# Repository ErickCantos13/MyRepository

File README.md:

# SensorEffector DMX Light Repository

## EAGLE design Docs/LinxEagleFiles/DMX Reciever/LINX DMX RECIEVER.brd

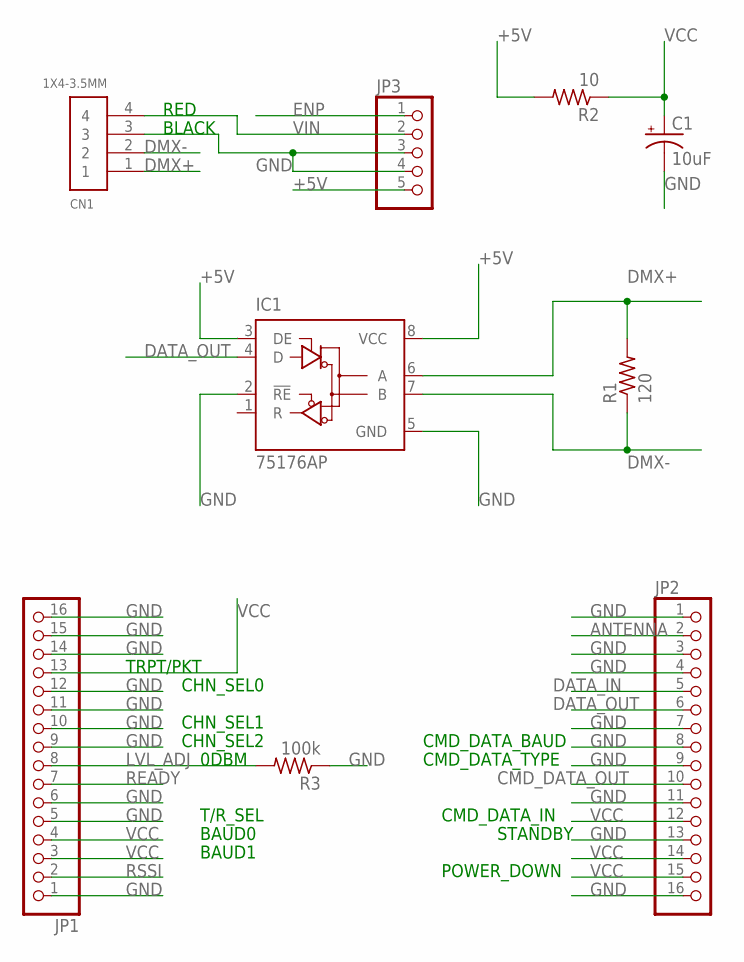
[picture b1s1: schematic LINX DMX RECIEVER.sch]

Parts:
C1: 10uF; B45181A
CN1: 1X4-3.5MM; 1X04-3.5MM
IC1: 75176AP; DIL08
JP1, JP2: PINHD-1X16; 1X16
JP3: PINHD-1X5/90; 1X05/90
R1: 120; 0414/15
R2: 10; 0414/15
R3: 100k; 0414/15

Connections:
+5V: IC1.3 (DE), IC1.8 (VCC), JP3.5, R2.2
ANTENNA: JP2.2
CMD_DATA_OUT: JP2.10
DATA_IN: JP2.5
DATA_OUT: IC1.4 (D), JP2.6
DMX+: CN1.1, IC1.6 (A), R1.2
DMX-: CN1.2, IC1.7 (B), R1.1
ENP: JP3.1
GND: C1.-, CN1.3, IC1.2 (!RE), IC1.5 (GND), JP1.1, JP1.5, JP1.6, JP1.9, JP1.10, JP1.11, JP1.12, JP1.14, JP1.15, JP1.16, JP2.1, JP2.3, JP2.4, JP2.7, JP2.8, JP2.9, JP2.11, JP2.13, JP2.16, JP3.3, JP3.4, R3.1
LVL_ADJ: JP1.8, R3.2
READY: JP1.7
RSSI: JP1.2
VCC: C1.+, JP1.3, JP1.4, JP1.13, JP2.12, JP2.14, JP2.15, R2.1
VIN: CN1.4, JP3.2

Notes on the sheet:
RED
BLACK
TRPT/PKT
CHN_SEL0
CHN_SEL1
CHN_SEL2
0DBM
T/R_SEL
BAUD0
BAUD1
STANDBY
POWER_DOWN
CMD_DATA_BAUD
CMD_DATA_TYPE
CMD_DATA_IN

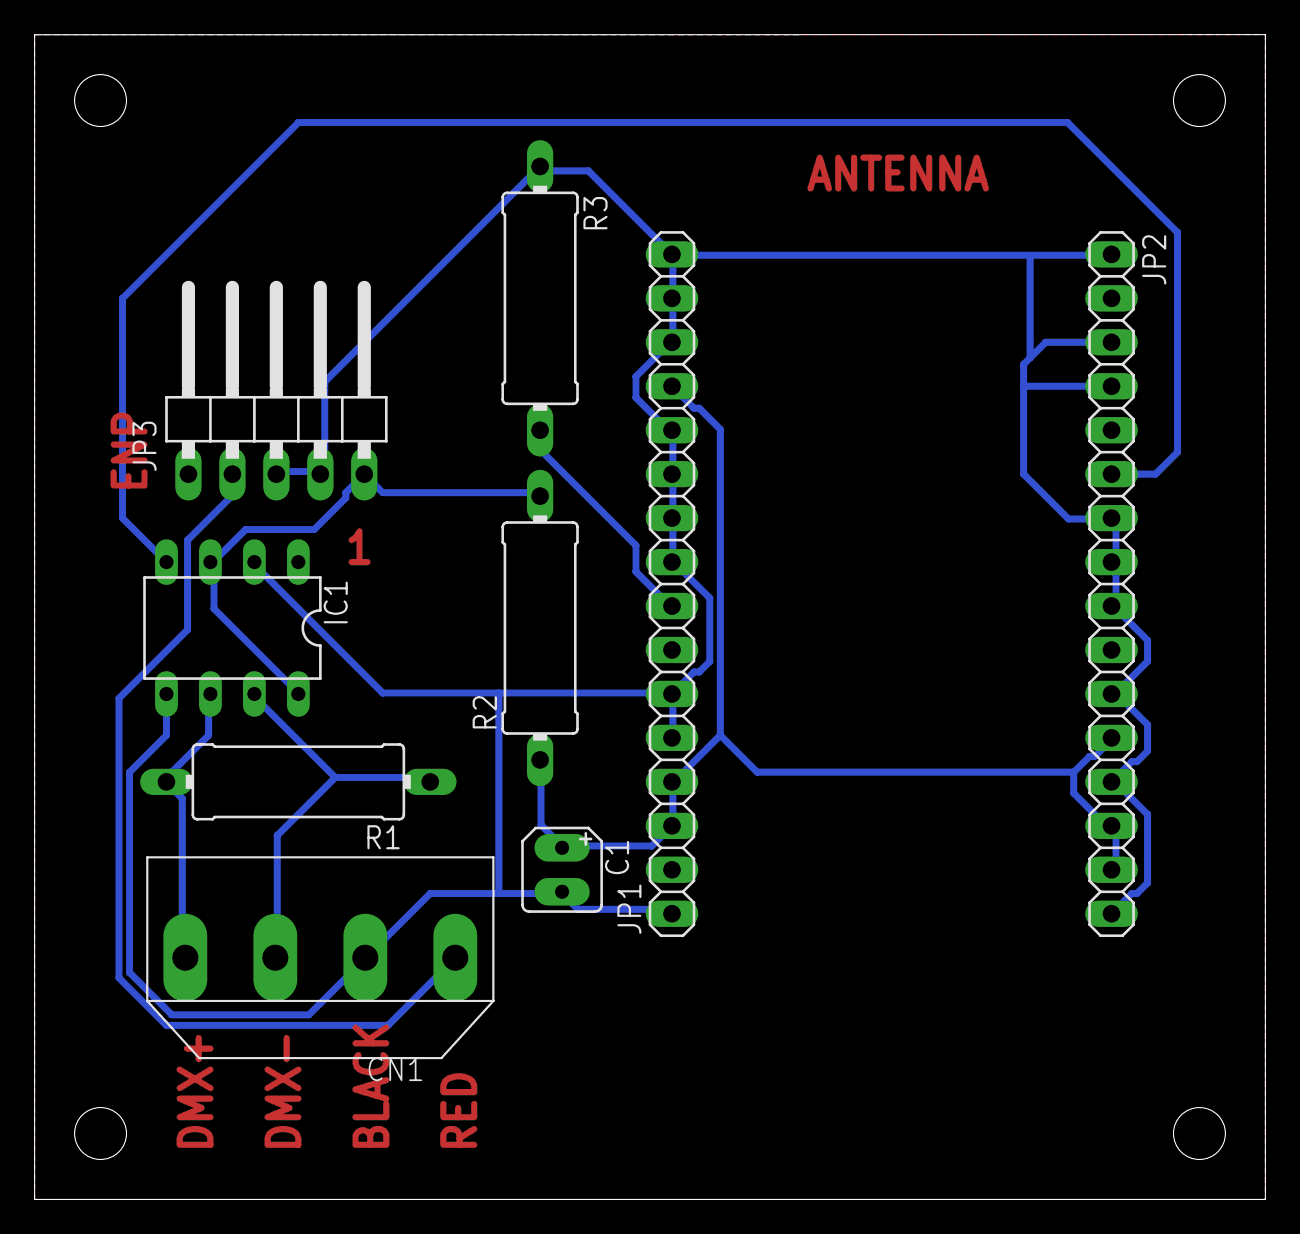
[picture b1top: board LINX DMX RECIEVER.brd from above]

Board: 2 copper layers, 71.1 x 67.3 mm, 9 parts (0 on the bottom side), 8 nets.

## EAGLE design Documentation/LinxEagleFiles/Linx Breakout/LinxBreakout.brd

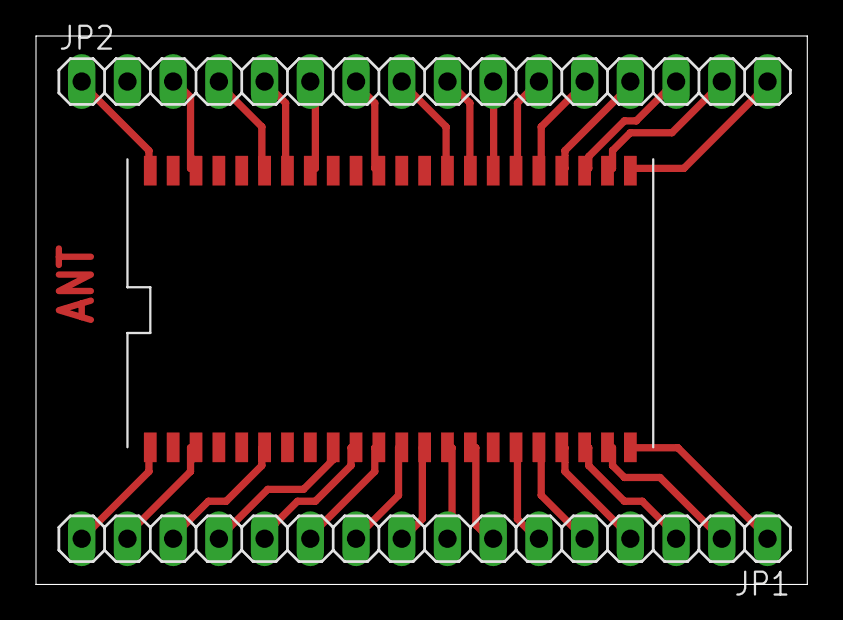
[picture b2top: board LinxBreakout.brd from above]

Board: 2 copper layers, 42.9 x 30.5 mm, 3 parts (0 on the bottom side), 31 nets.

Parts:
JP1, JP2: 1X16
U$1: TRM-900-NT

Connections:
unnamed: JP1.16, U$1.PIN1-GND
unnamed: JP1.15, U$1.PIN3-GND
unnamed: JP1.14, U$1.PIN6-GND
unnamed: JP1.13, U$1.PIN9-TRPT/PKT
unnamed: JP1.12, U$1.PIN10-CHN_SEL0
unnamed: JP1.11, U$1.PIN11-GND
unnamed: JP1.10, U$1.PIN12-CHN_SEL1
unnamed: JP1.9, U$1.PIN13-CHN_SEL2
unnamed: JP1.8, U$1.PIN14-LVL_ADJ
unnamed: JP1.7, U$1.PIN15-READY
unnamed: JP1.6, U$1.PIN17-GND
unnamed: JP1.5, U$1.PIN18-T/R_SEL
unnamed: JP1.4, U$1.PIN19-BAUD0
unnamed: JP1.3, U$1.PIN20-BAUD1
unnamed: JP1.2, U$1.PIN21-RSSI
unnamed: JP1.1, U$1.PIN22-GND
unnamed: JP2.1, U$1.PIN44-GND
unnamed: JP2.3, U$1.PIN42-GND
unnamed: JP2.4, U$1.PIN39-GND
unnamed: JP2.5, U$1.PIN38-DATA_IN
unnamed: JP2.6, U$1.PIN37-DATA_OUT
unnamed: JP2.7, U$1.PIN34-GND
unnamed: JP2.8, U$1.PIN31-CMD_DATA_BAUD
unnamed: JP2.9, U$1.PIN30-CMD_DATA_TYPE
unnamed: JP2.10, U$1.PIN29-CMD_DATA_OUT
unnamed: JP2.11, U$1.PIN28-GND
unnamed: JP2.12, U$1.PIN27-CMD_DATA_IN
unnamed: JP2.13, U$1.PIN26-STANDBY
unnamed: JP2.14, U$1.PIN25-VCC
unnamed: JP2.15, U$1.PIN24-POWER_DOWN
unnamed: JP2.16, U$1.PIN23-GND

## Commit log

2017-09-23 Uploading Documentation Templates
2017-09-23 Proposal update
    Adding few changes for clearer picture on project focuses.
2017-09-23 Proposal Update
    minor change
2017-10-03 Budget
2017-10-09 Revised Propsal
2017-10-09 Proposal
2017-10-09 Budget PDF
2017-10-09 pdf budget
2017-10-09 BudgetImage
2017-12-01 Raspberry pi images
2017-12-08 placard
2017-12-12 placard update
2018-01-09 Updated Budget
    Included DMX board and schematic files.
2018-01-09 Organizing directories
